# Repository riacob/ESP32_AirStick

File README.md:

# ESP32 AirStick

The board is currently in Rev2

## Features
- AHT20 Temperature & Humidity Sensor
- ENS160 eCO2, AQI, TVOCs Sensor
- Measured TVOCs and their range:
  - Ethanol 0-6 ppm
  - Hydrogen 0-10 ppm
  - Acetone 0-32 ppm
  - Carbon Monoxide 0-90 ppm
  - Toluene 0-32 ppm
- 18650 Li-ion battery holder, TP4057 charging circuitry
- Battery protection with fuse and DW03
- USB Type-C with USB CDC for emulated UART and charging, ESD protected
- MicroSD TF card slot for data logging
- ESP32C3 For WiFi and BLE connectivity
- Still work in progress, compatible with [BLEMQTTPair]() app
- WS2812B led for indication and alarm
- Optional SSD1306 OLED 
- 75dB magnetic buzzer for alarm
- SparkFun Qwiic connector, in JST-SH 1.0mm pitch connector
- Optional connector to bring the rst and boot buttons to a remote front panel
- Low power, long life, high efficiency circuitry for optimized battery use
- Low BOM cost, consolidated parts, robust layout

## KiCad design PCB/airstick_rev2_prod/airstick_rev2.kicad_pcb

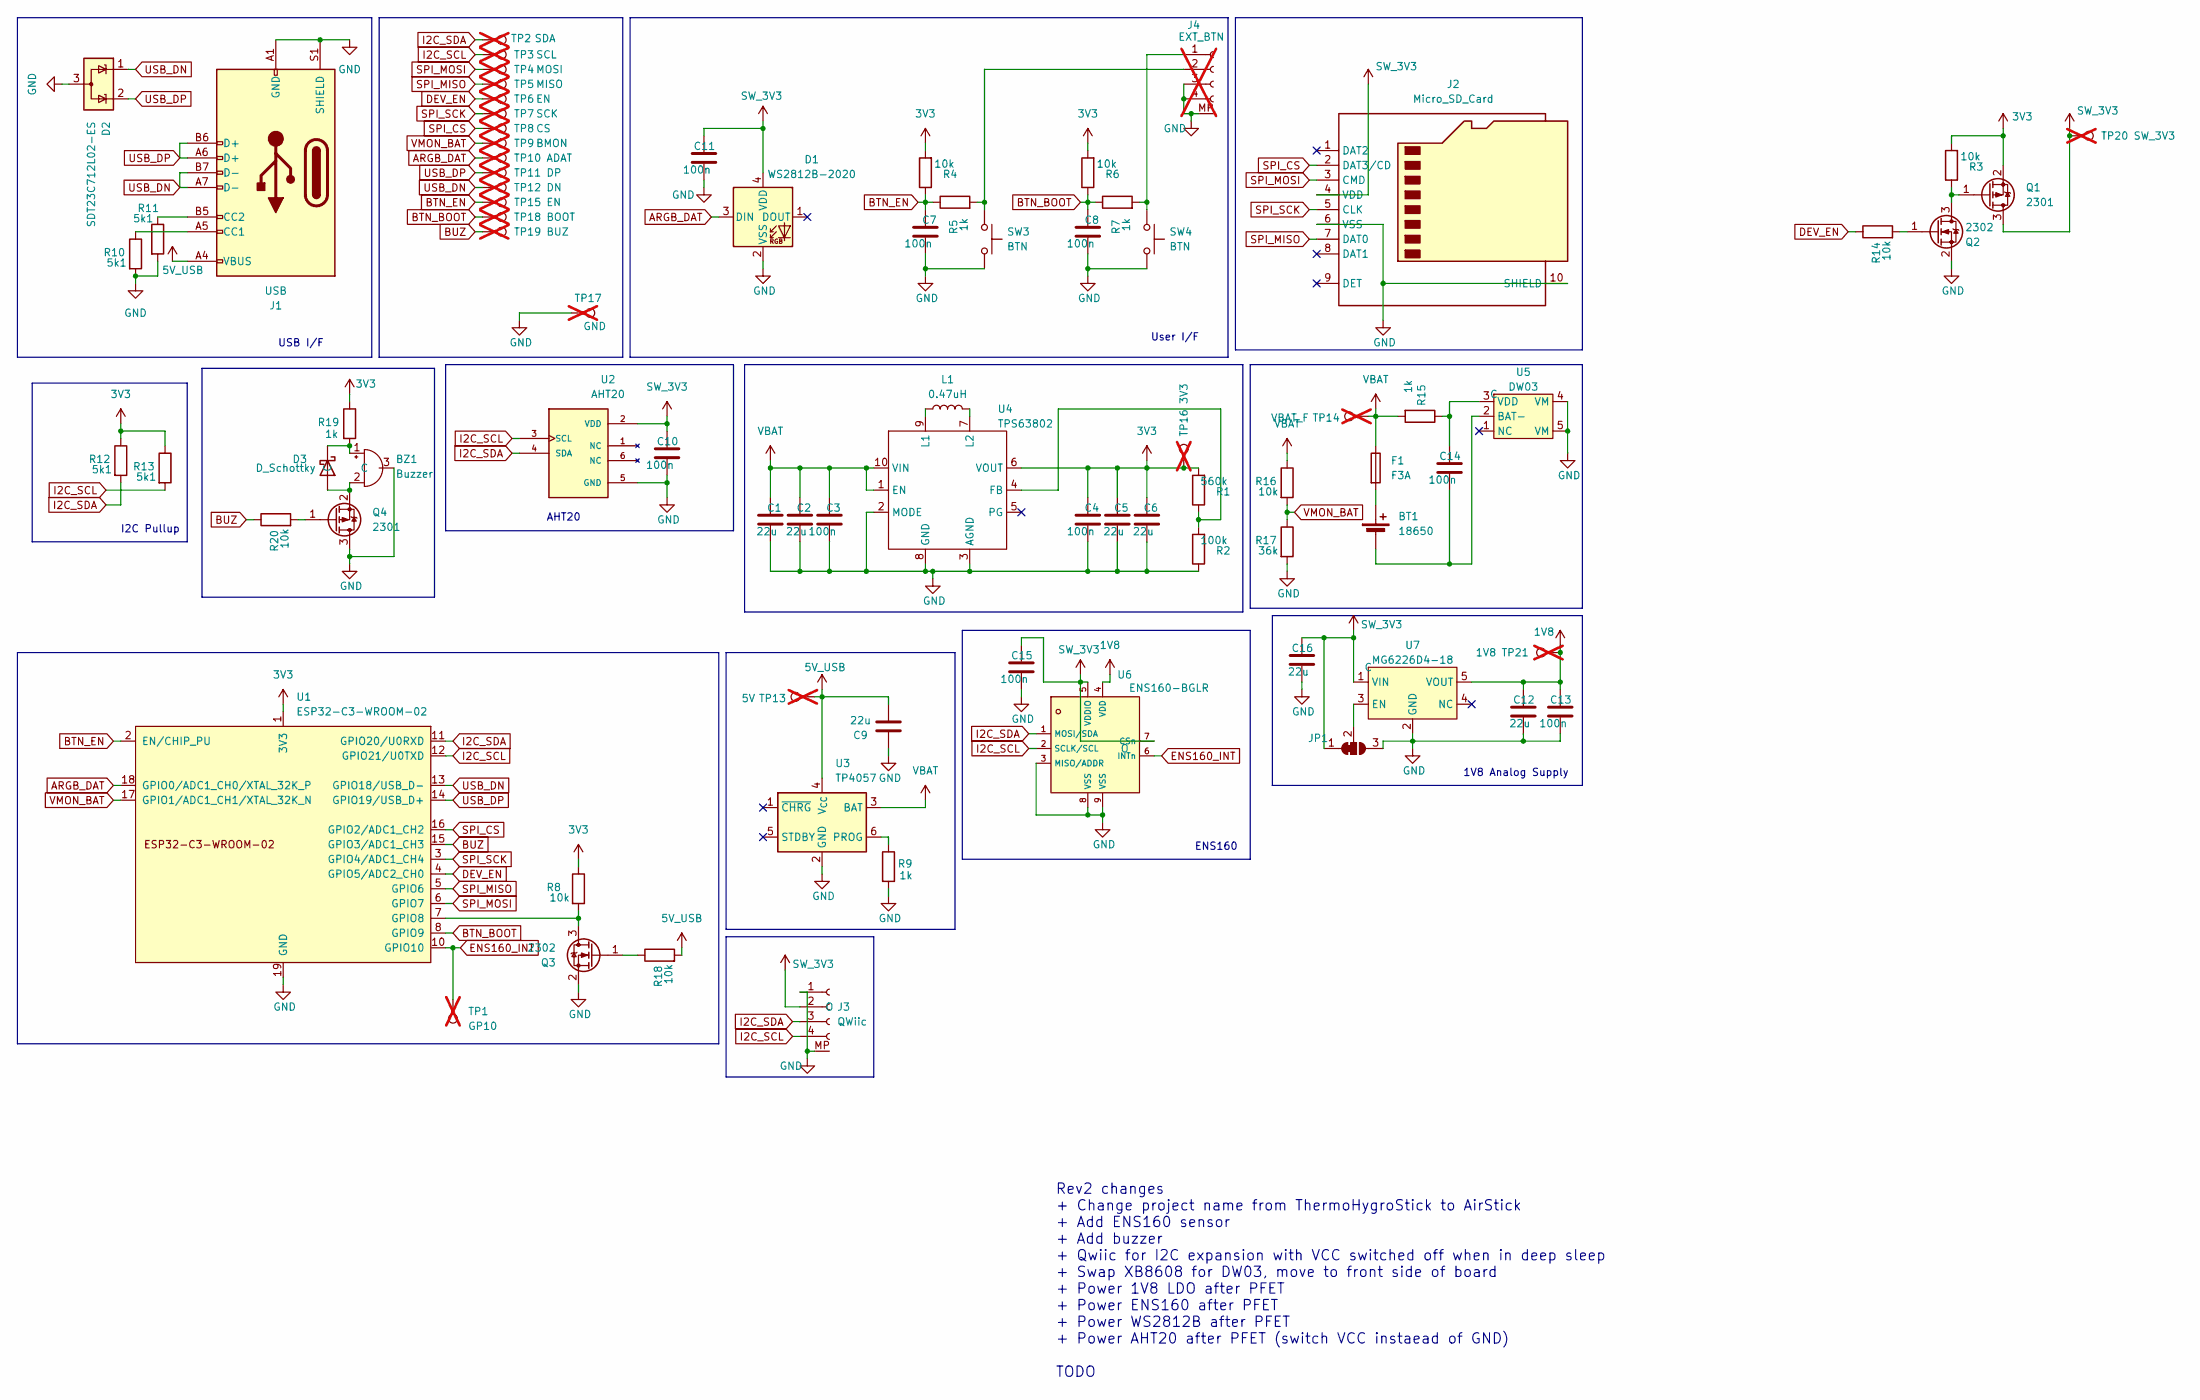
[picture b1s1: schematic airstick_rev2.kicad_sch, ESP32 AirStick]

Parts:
BT1: 18650; BatteryHolder_Keystone_1042_1x18650; LCSC C2988620
BZ1: Buzzer; BUZ-SMD_FST-5020; LCSC C391029
C1, C2, C5, C6, C9, C12, C16: 22u; C_0603_1608Metric; LCSC C159801
C3, C4, C7, C8, C10, C11, C13, C14, C15: 100n; C_0603_1608Metric; LCSC C1729
D1: WS2812B-2020; LED_WS2812B-2020_PLCC4_2.0x2.0mm; LCSC C5349955
D2: SDT23C712L02-ES; SOT-23-3; LCSC C5180269
D3: D_Schottky; SOD-723_L1.7-W1.0-P1.42-RD; LCSC C8525
F1: F3A; Fuse_1206_3216Metric; LCSC C163126
J1: USB; USB_C_Receptacle_G-Switch_GT-USB-7010ASV; LCSC C2988369
J2: Micro_SD_Card; J_SD_Card-micro_socket_A; LCSC C2988369
J3: QWiic; JST_SH_BM04B-SRSS-TB_1x04-1MP_P1.00mm_Vertical
J4: EXT_BTN; JST_SH_BM04B-SRSS-TB_1x04-1MP_P1.00mm_Vertical; not fitted
JP1: SolderJumper_3_Bridged12; SolderJumper-3_P1.3mm_Bridged12_RoundedPad1.0x1.5mm
L1: 0.47uH; L_SMD_7.1x6.6mm; LCSC C22463816
Q1, Q4: 2301; SOT-23; LCSC C41384537
Q2, Q3: 2302; SOT-23; LCSC C41384540
R1: 560k; R_0603_1608Metric; LCSC C17414
R2: 100k; R_0603_1608Metric; LCSC C17414
R3, R4, R6, R8, R14, R16, R18, R20: 10k; R_0603_1608Metric; LCSC C17414
R5, R7, R9, R15, R19: 1k; R_0603_1608Metric; LCSC C17414
R10, R11, R12, R13: 5k1; R_0603_1608Metric; LCSC C17414
R17: 36k; R_0603_1608Metric; LCSC C17414
SW3, SW4: BTN; SW_Push_1P1T_NO_6x6mm_H9.5mm; LCSC C2888455
TP1: GP10; TestPoint_Pad_D1.0mm_NoSilk; not fitted
TP2: SDA; TestPoint_Pad_D1.0mm_NoSilk; not fitted
TP3: SCL; TestPoint_Pad_D1.0mm_NoSilk; not fitted
TP4: MOSI; TestPoint_Pad_D1.0mm_NoSilk; not fitted
TP5: MISO; TestPoint_Pad_D1.0mm_NoSilk; not fitted
TP6, TP15: EN; TestPoint_Pad_D1.0mm_NoSilk; not fitted
TP7: SCK; TestPoint_Pad_D1.0mm_NoSilk; not fitted
TP8: CS; TestPoint_Pad_D1.0mm_NoSilk; not fitted
TP9: BMON; TestPoint_Pad_D1.0mm_NoSilk; not fitted
TP10: ADAT; TestPoint_Pad_D1.0mm_NoSilk; not fitted
TP11: DP; TestPoint_Pad_D1.0mm_NoSilk; not fitted
TP12: DN; TestPoint_Pad_D1.0mm_NoSilk; not fitted
TP13: 5V; TestPoint_Pad_D1.0mm_NoSilk; not fitted
TP14: VBAT_F; TestPoint_Pad_D1.0mm_NoSilk; not fitted
TP16: 3V3; TestPoint_Pad_D1.0mm_NoSilk; not fitted
TP17: GND; TestPoint_Pad_4.0x4.0mm; not fitted
TP18: BOOT; TestPoint_Pad_D1.0mm_NoSilk; not fitted
TP19: BUZ; TestPoint_Pad_D1.0mm_NoSilk; not fitted
TP20: SW_3V3; TestPoint_Pad_D1.0mm_NoSilk; not fitted
TP21: 1V8; TestPoint_Pad_D1.0mm_NoSilk; not fitted
U1: ESP32-C3-WROOM-02; LCSC C2934560
U2: AHT20; PSON100P300X300X110-6N; PARTREV V1.0; LCSC C2757850
U3: TP4057; SOT-23-6; LCSC C20199358
U4: TPS63802; DLA0010A; LCSC C1849531
U5: DW03; SOT-23-5
U6: ENS160-BGLR; LGA-9_L3.0-W3.0-R3-C3-P1.05-TL; LCSC C3659351
U7: MG6226D4-18; Texas_X2SON-4_1x1mm_P0.65mm; LCSC C22396246

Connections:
1V8: C12.1, C13.1, TP21.1, U6.4 (VDD), U7.5 (VOUT)
3V3: C4.1, C5.1, C6.1, Q1.2 (S), R1.2, R3.2, R4.2, R6.2, R8.1, R12.1, R13.1, R19.1, TP16.1, U1.1 (3V3), U4.6 (VOUT)
5V_USB: C9.2, J1.A4 (VBUS), J1.A9 (VBUS), J1.B4 (VBUS), J1.B9 (VBUS), R18.2, TP13.1, U3.4 (V_{CC})
ARGB_DAT: D1.3 (DIN), TP10.1, U1.18 (GPIO0/ADC1_CH0/XTAL_32K_P)
BTN_BOOT: C8.1, R6.1, R7.1, TP18.1, U1.8 (GPIO9)
BTN_EN: C7.1, R4.1, R5.1, TP15.1, U1.2 (EN/CHIP_PU)
BUZ: R20.1, TP19.1, U1.15 (GPIO3/ADC1_CH3)
DEV_EN: R14.1, TP6.1, U1.4 (GPIO5/ADC2_CH0)
ENS160_INT: TP1.1, U1.10 (GPIO10), U6.6 (INTn)
GND: BZ1.3 (-), C1.2, C2.2, C3.2, C4.2, C5.2, C6.2, C7.2, C8.2, C9.1, C10.2, C11.2, C12.2, C13.2, C15.2, C16.2, D1.2 (VSS), D2.3 (A), J1.A1 (GND), J1.A12 (GND), J1.B1 (GND), J1.B12 (GND), J1.S1 (SHIELD), J2.6 (VSS), J2.10 (SHIELD), J3.1, J3.MP, J4.3, J4.4, J4.MP, JP1.3 (B), Q2.2 (S), Q3.2 (S), Q4.3 (D), R2.1, R9.2, R10.2, R11.2, R17.2, SW3.2, SW4.2, TP17.1, U1.9 (GND), U1.19 (GND), U2.5 (GND), U3.2 (GND), U4.2 (MODE), U4.3 (AGND), U4.8 (GND), U5.4 (VM), U5.5 (VM), U6.3 (MISO/ADDR), U6.8 (VSS), U6.9 (VSS), U7.2 (GND)
I2C_SCL: J3.4, R13.2, TP3.1, U1.12 (GPIO21/U0TXD), U2.3 (SCL), U6.2 (SCLK/SCL)
I2C_SDA: J3.3, R12.2, TP2.1, U1.11 (GPIO20/U0RXD), U2.4 (SDA), U6.1 (MOSI/SDA)
unnamed: BT1.1 (+), F1.2
unnamed: BT1.2 (-), C14.2, U5.2 (BAT-)
unnamed: BZ1.1 (+), D3.1 (K), R19.2
unnamed: BZ1.2 (-), D3.2 (A), Q4.2 (S)
unnamed: J1.A5 (CC1), R10.1
unnamed: J1.B5 (CC2), R11.1
unnamed: J4.1, R7.2, SW4.1
unnamed: J4.2, R5.2, SW3.1
unnamed: JP1.2 (C), U7.3 (EN)
unnamed: Q1.1 (G), Q2.3 (D), R3.1
unnamed: Q2.1 (G), R14.2
unnamed: Q3.3 (D), R8.2, U1.7 (GPIO8)
unnamed: Q3.1 (G), R18.1
unnamed: Q4.1 (G), R20.2
unnamed: R9.1, U3.6 (PROG)
unnamed: R1.1, R2.2, U4.4 (FB)
unnamed: L1.1, U4.9 (L1)
unnamed: L1.2, U4.7 (L2)
unnamed: C14.1, R15.1, U5.3 (VDD)
SPI_CS: J2.2 (DAT3/CD), TP8.1, U1.16 (GPIO2/ADC1_CH2)
SPI_MISO: J2.7 (DAT0), TP5.1, U1.5 (GPIO6)
SPI_MOSI: J2.3 (CMD), TP4.1, U1.6 (GPIO7)
SPI_SCK: J2.5 (CLK), TP7.1, U1.3 (GPIO4/ADC1_CH4)
SW_3V3: C10.1, C11.1, C15.1, C16.1, D1.4 (VDD), J2.4 (VDD), J3.2, JP1.1 (A), Q1.3 (D), TP20.1, U2.2 (VDD), U6.5 (VDDIO), U6.7 (CSn), U7.1 (VIN)
USB_DN: D2.1 (K), J1.A7 (D-), J1.B7 (D-), TP12.1, U1.13 (GPIO18/USB_D-)
USB_DP: D2.2 (K), J1.A6 (D+), J1.B6 (D+), TP11.1, U1.14 (GPIO19/USB_D+)
VBAT: C1.1, C2.1, C3.1, F1.1, R15.2, R16.1, TP14.1, U3.3 (BAT), U4.1 (EN), U4.10 (VIN)
VMON_BAT: R16.2, R17.1, TP9.1, U1.17 (GPIO1/ADC1_CH1/XTAL_32K_N)

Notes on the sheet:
1V8 Analog Supply
Rev2 changes + Change project name from ThermoHygroStick to AirStick + Add ENS160 sensor + Add buzzer + Qwiic for I2C expansion with VCC switched off when in deep sleep + Swap XB8608 for DW03, move to front side of board + Power 1V8 LDO after PFET + Power ENS160 after PFET + Power WS2812B after PFE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
AHT20
I2C Pullup
USB I/F
User I/F
ENS160

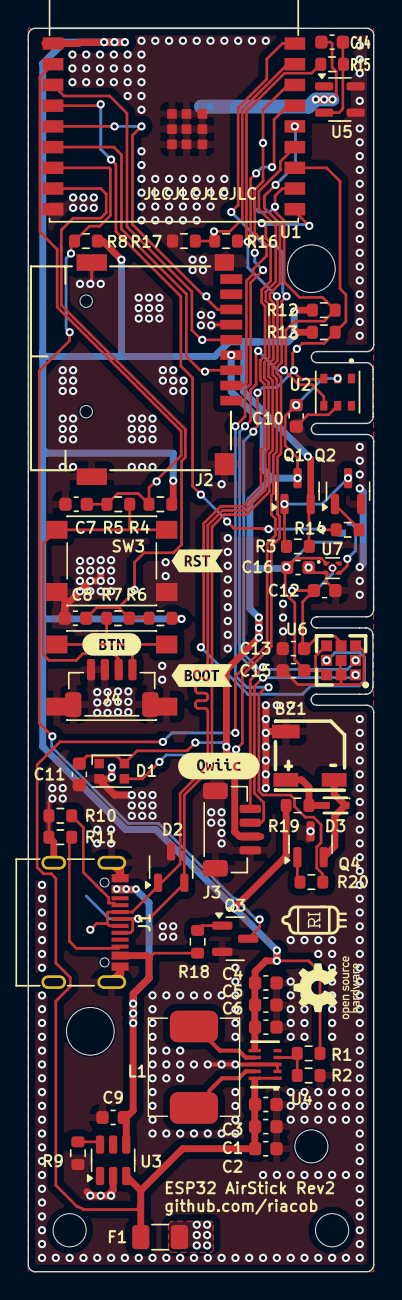
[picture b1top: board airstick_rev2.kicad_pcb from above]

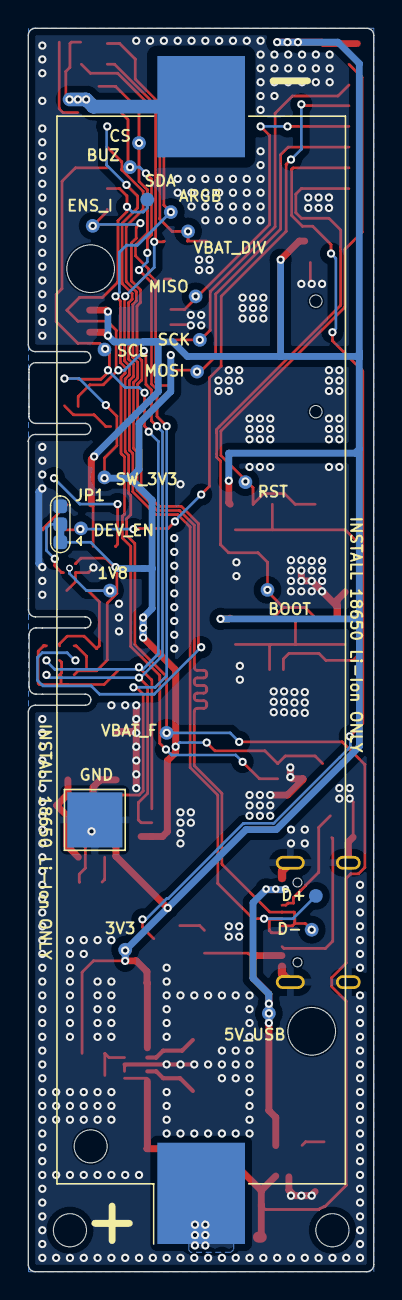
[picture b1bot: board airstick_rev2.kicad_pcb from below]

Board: 2 copper layers, 25.0 x 90.0 mm, 86 parts (23 on the bottom side), 40 nets.

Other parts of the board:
kibuzzard-67BA5A9B: G***; kibuzzard-67BA5A9B
kibuzzard-67BA57D8: G***; kibuzzard-67BA57D8
kibuzzard-67BA587D: G***; kibuzzard-67BA587D
kibuzzard-67BA5873: G***; kibuzzard-67BA5873

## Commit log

2025-02-24 tidy schematic
2025-02-24 add README.md
